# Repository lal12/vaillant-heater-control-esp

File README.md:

# Vaillant heater control

This project contains a little board (and software) to control a Vaillant heater.

It is currently Work in Progress and not everything works!!

## PCB

/kicad

The schematic shows a PCB which controls the Vaillant heater via 789 interface which is just an analog voltage to control the flow temperature (Vorlauftemperatur).

## Esphome

/esphome

A simple config to use the PCB with an ESP32.

## NodeJS

/nodejs

Small NodeJS application, it reads out the data from the heater.
It isn't really well made and more intended for temporary and debugging purposes.

It will log the data to the console and a json log.
It will display a graph on a little webpage.
It will publish the data to mqtt in a HomeAssistant compatible format.

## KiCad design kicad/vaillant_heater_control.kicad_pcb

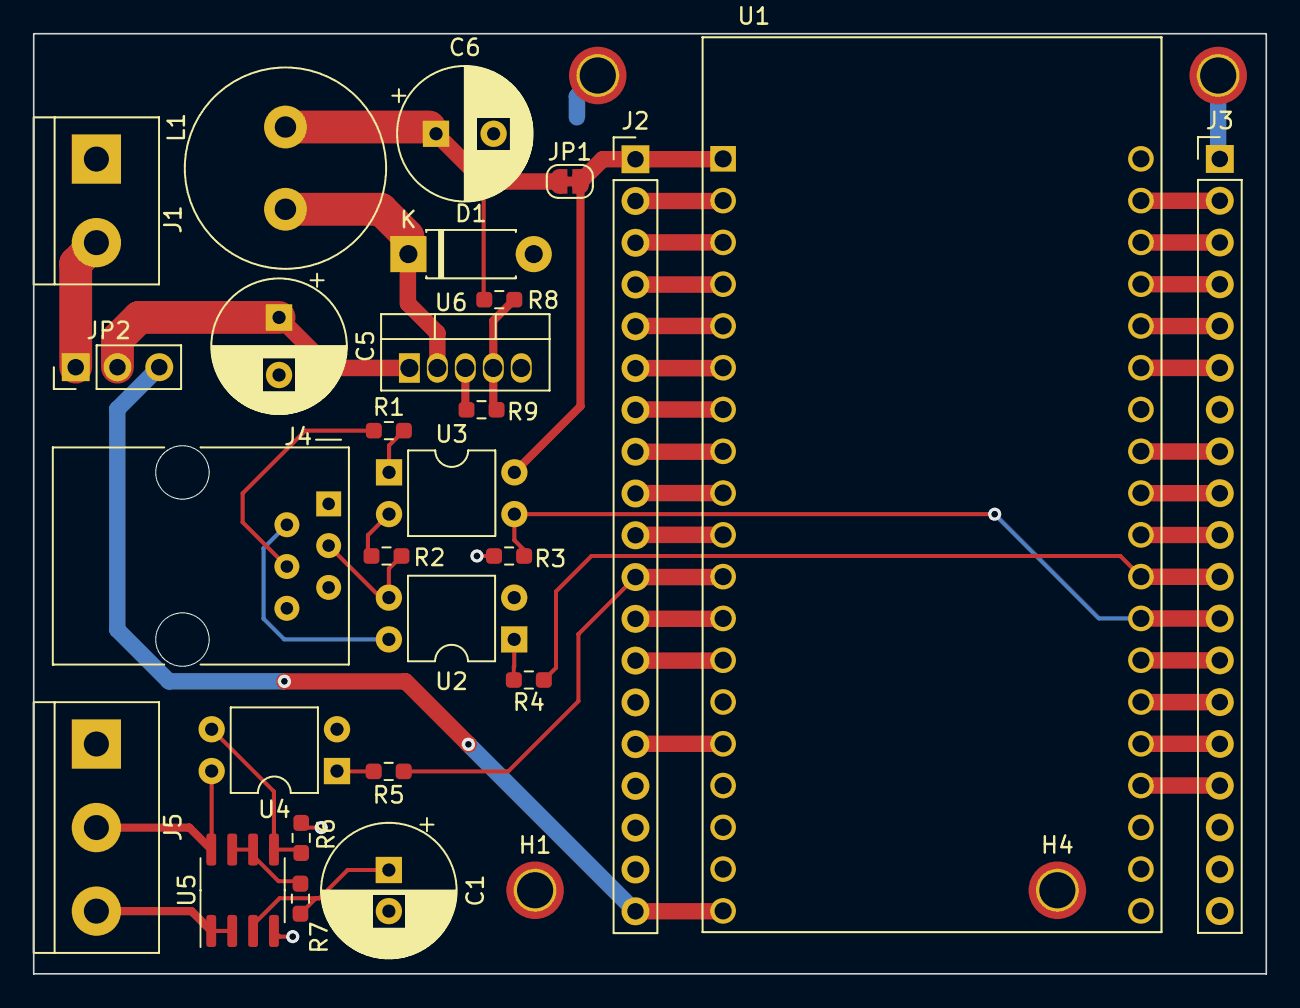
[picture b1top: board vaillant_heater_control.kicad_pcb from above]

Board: 2 copper layers, 74.9 x 57.2 mm, 31 parts (0 on the bottom side), 48 nets.

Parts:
C1: 10u; CP_Radial_D8.0mm_P2.50mm
C5: 100u; CP_Radial_D8.0mm_P3.50mm
C6: 330u; CP_Radial_D8.0mm_P3.50mm
D1: 1n5819; D_DO-41_SOD81_P7.62mm_Horizontal
H1, H2, H3, H4: MountingHole_Pad; MountingHole_2.2mm_M2_ISO7380_Pad_TopBottom
J1: Screw_Terminal_01x02; TerminalBlock_bornier-2_P5.08mm
J2, J3: Conn_01x19; PinHeader_1x19_P2.54mm_Vertical
J4: 6P6C; RJ12_Amphenol_54601
J5: Screw_Terminal_01x03; TerminalBlock_bornier-3_P5.08mm
JP1: SolderJumper_2_Bridged; SolderJumper-2_P1.3mm_Bridged_RoundedPad1.0x1.5mm
JP2: Jumper_3_Bridged12; PinHeader_1x03_P2.54mm_Vertical
L1: 330u; L_Radial_D12.0mm_P5.00mm_Fastron_11P
R1, R5: 350; R_0603_1608Metric_Pad0.98x0.95mm_HandSolder
R2, R3, R6: 10k; R_0603_1608Metric_Pad0.98x0.95mm_HandSolder
R4: 180; R_0603_1608Metric_Pad0.98x0.95mm_HandSolder
R7: 500; R_0603_1608Metric_Pad0.98x0.95mm_HandSolder
R8: 3.4k; R_0603_1608Metric_Pad0.98x0.95mm_HandSolder
R9: 2k; R_0603_1608Metric_Pad0.98x0.95mm_HandSolder
U1: ESP32-DEVKITC-32D; MODULE_ESP32-DEVKITC-32D
U2, U3, U4: SFH617A-1; DIP-4_W7.62mm
U5: LM358; SOIC-8_3.9x4.9mm_P1.27mm
U6: LM2575BT-ADJ; TO-220-5_Vertical

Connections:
+3V3: J2.1, JP1.2 (B), U1.1 (3V3), U3.4
/789_analog/CTRL: J5.3, U5.1, U5.2 (-)
/789_analog/GND_789: C1.2, J5.1, R6.1, U5.4 (V-)
/789_analog/V_789: J5.2, U4.4, U5.8 (V+)
/power supply/PS_3V3: C6.1, JP1.1 (A), L1.2, R8.2
/power supply/Vin: C5.1, JP2.2 (C), U6.1 (VIN)
/serial/X6_5V: J4.2, U2.4
/serial/X6_GND: J4.5, R2.2, U3.2
/serial/X6_RXD: J4.3, R2.1, U2.3
/serial/X6_TXD: J4.4, R1.1
GND: C5.2, C6.2, D1.2 (A), H1.1, H2.1, H3.1, H4.1, J1.1, J2.14, J3.1, J3.7, R3.2, R9.1, U1.14 (GND1), U1.20 (GND3), U1.26 (GND2), U2.2, U4.2, U6.3 (GND), U6.5 (~ON/OFF)
IO27: J2.11, R5.1, U1.11 (IO27)
unnamed: C1.1, R7.2, U5.3 (+)
unnamed: J1.2, JP2.1 (A)
unnamed: J2.2, U1.2 (EN)
unnamed: J2.3, U1.3 (SENSOR_VP)
unnamed: J2.4, U1.4 (SENSOR_VN)
unnamed: J2.5, U1.5 (IO34)
unnamed: J2.6, U1.6 (IO35)
unnamed: J2.7, U1.7 (IO32)
unnamed: J2.8, U1.8 (IO33)
unnamed: J2.9, U1.9 (IO25)
unnamed: J2.10, U1.10 (IO26)
unnamed: J2.12, U1.12 (IO14)
unnamed: J2.13, U1.13 (IO12)
unnamed: J2.15, U1.15 (IO13)
unnamed: J3.2, U1.21 (IO23)
unnamed: J3.3, U1.22 (IO22)
unnamed: J3.4, U1.23 (TXD0)
unnamed: J3.5, U1.24 (RXD0)
unnamed: J3.6, U1.25 (IO21)
unnamed: J3.8, U1.27 (IO19)
unnamed: J3.9, U1.28 (IO18)
unnamed: J3.10, U1.29 (IO5)
unnamed: J3.13, U1.32 (IO4)
unnamed: J3.14, U1.33 (IO0)
unnamed: J3.15, U1.34 (IO2)
unnamed: J3.16, U1.35 (IO15)
unnamed: D1.1 (K), L1.1, U6.2 (OUT)
unnamed: R1.2, U3.1
unnamed: R4.1, U2.1
unnamed: R5.2, U4.1
unnamed: R6.2, U4.3, U5.5 (+)
unnamed: R7.1, U5.6 (-), U5.7
unnamed: R8.1, R9.2, U6.4 (FB)
RX: J3.12, R3.1, U1.31 (IO16), U3.3
TX: J3.11, R4.2, U1.30 (IO17)
V_USB: J2.19, JP2.3 (B), U1.19 (EXT_5V)

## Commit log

2022-10-05 Added files to read out the vaillant heater with nodejs
2022-10-05 Updated README Added nodejs/.gitignore
